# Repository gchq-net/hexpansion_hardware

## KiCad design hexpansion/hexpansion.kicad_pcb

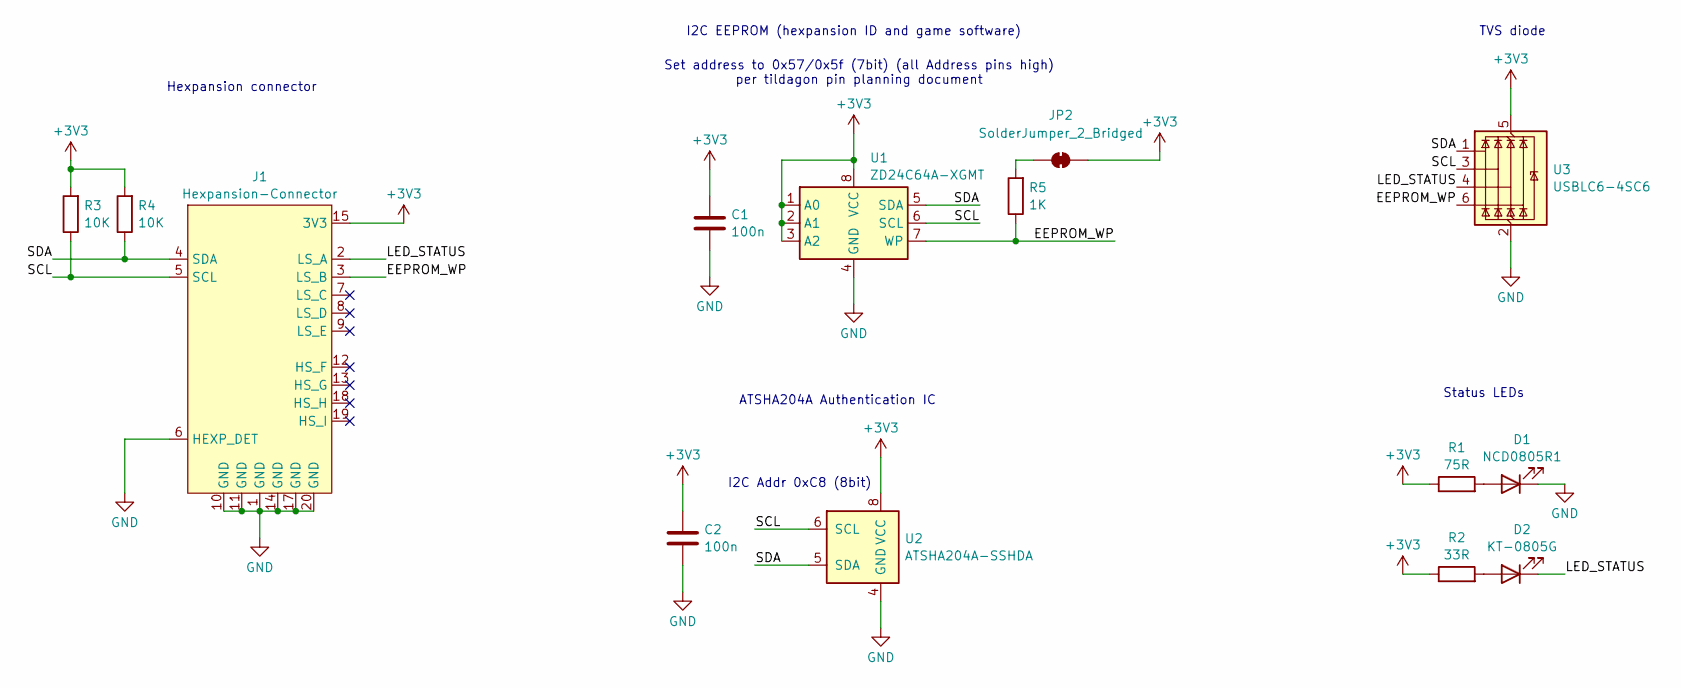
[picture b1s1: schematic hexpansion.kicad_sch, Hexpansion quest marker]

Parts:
C1, C2: 100n; C_0603_1608Metric
D1: NCD0805R1; LED_0805_2012Metric
D2: KT-0805G; LED_0805_2012Metric
J1: Hexpansion-Connector; hexpansion-edge-connector
JP2: SolderJumper_2_Bridged; SolderJumper-2_P1.3mm_Bridged_RoundedPad1.0x1.5mm
R1: 75R; R_0603_1608Metric
R2: 33R; R_0603_1608Metric
R3, R4: 10K; R_0603_1608Metric
R5: 1K; R_0603_1608Metric
U1: ZD24C64A-XGMT; TSSOP-8_4.4x3mm_P0.65mm
U2: ATSHA204A-SSHDA; SOIC-8_3.9x4.9mm_P1.27mm
U3: USBLC6-4SC6; SOT-23-6

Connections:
+3V3: C1.1, C2.1, J1.15 (3V3), J1.16 (3V3), JP2.2 (B), R1.1, R2.1, R3.2, R4.2, U1.1 (A0), U1.2 (A1), U1.3 (A2), U1.8 (VCC), U2.8 (VCC), U3.5 (VBUS)
/EEPROM_WP: J1.3 (LS_B), R5.1, U1.7 (WP), U3.6 (I/O4)
/LED_STATUS: D2.1 (K), J1.2 (LS_A), U3.4 (I/O3)
/SCL: J1.5 (SCL), R3.1, U1.6 (SCL), U2.6 (SCL), U3.3 (I/O2)
/SDA: J1.4 (SDA), R4.1, U1.5 (SDA), U2.5 (SDA), U3.1 (I/O1)
GND: C1.2, C2.2, D1.1 (K), J1.1 (GND), J1.6 (HEXP_DET), J1.10 (GND), J1.11 (GND), J1.14 (GND), J1.17 (GND), J1.20 (GND), U1.4 (GND), U2.4 (GND), U3.2 (GND)
unnamed: D1.2 (A), R1.2
unnamed: D2.2 (A), R2.2
unnamed: JP2.1 (A), R5.2

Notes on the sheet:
ATSHA204A Authentication IC
Set address to 0x57/0x5f (7bit) (all Address pins high) per tildagon pin planning document
I2C Addr 0xC8 (8bit)
Status LEDs
Hexpansion connector
I2C EEPROM (hexpansion ID and game software)
TVS diode

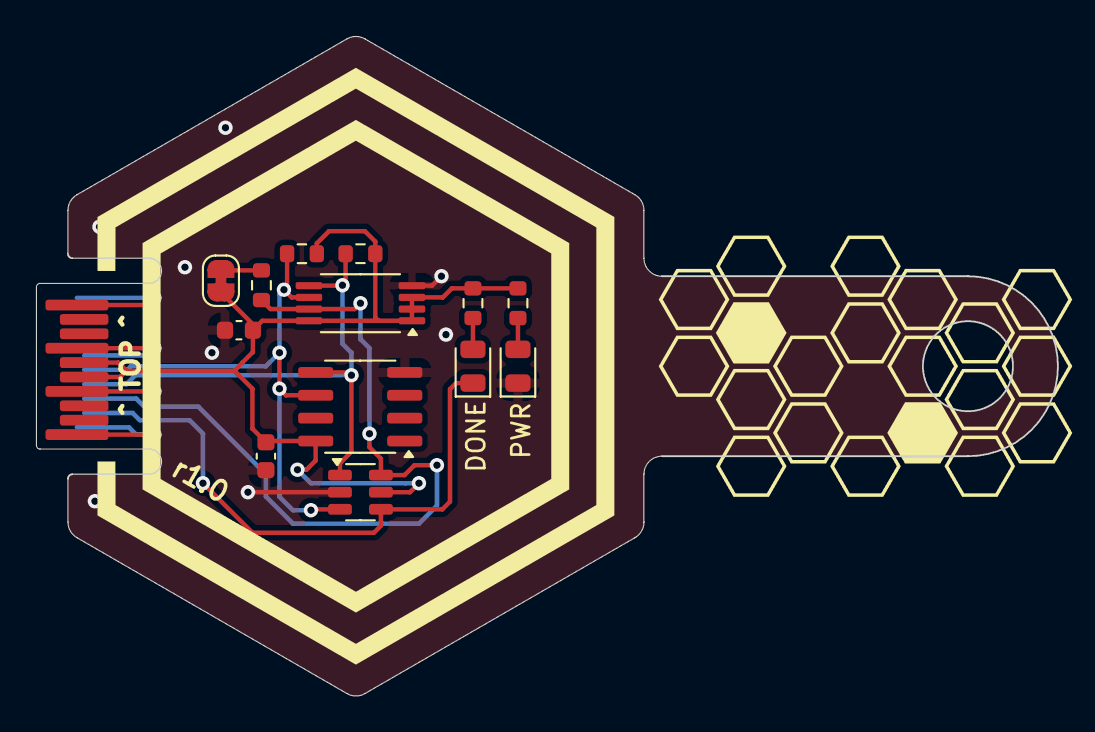
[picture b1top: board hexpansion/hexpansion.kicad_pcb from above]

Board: 2 copper layers, 56.7 x 36.6 mm, 14 parts (0 on the bottom side), 9 nets.

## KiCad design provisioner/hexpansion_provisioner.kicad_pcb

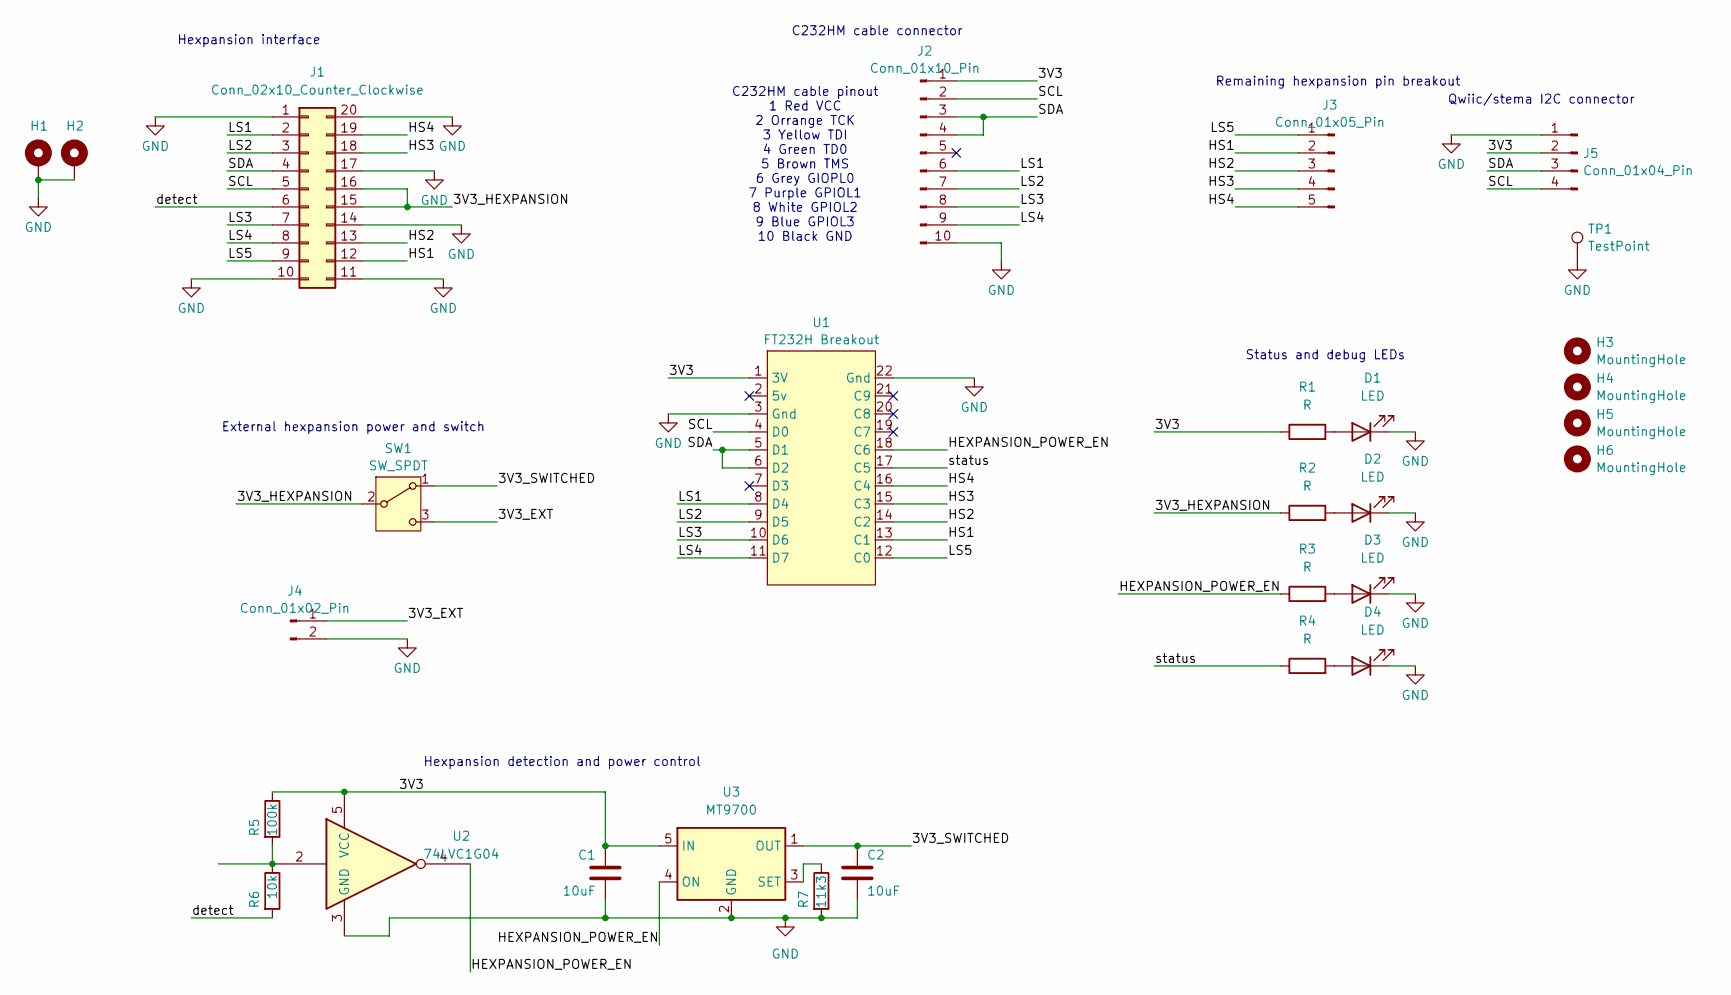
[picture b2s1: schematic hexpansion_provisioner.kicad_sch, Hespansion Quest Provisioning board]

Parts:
C1, C2: 10uF; C_1206_3216Metric
D1, D2, D3, D4: LED; LED_0805_2012Metric
H1, H2: MountingHole_Pad; SMTSO2030CTJ
H3, H4, H5, H6: MountingHole; MountingHole_2.7mm_M2.5
J1: Conn_02x10_Counter_Clockwise; SFP
J2: Conn_01x10_Pin; PinHeader_1x10_P2.54mm_Vertical
J3: Conn_01x05_Pin; PinHeader_1x05_P2.54mm_Vertical
J4: Conn_01x02_Pin; PinHeader_1x02_P2.54mm_Vertical
J5: Conn_01x04_Pin; JST_SH_SM04B-SRSS-TB_1x04-1MP_P1.00mm_Horizontal
R1, R2, R3, R4: R; R_0603_1608Metric
R5: 100k; R_0402_1005Metric
R6: 10k; R_0402_1005Metric
R7: 11k3; R_0603_1608Metric
SW1: SW_SPDT; SW_SPDT_PCM12
TP1: TestPoint; TestPoint_Bridge_Pitch5.08mm_Drill0.7mm
U1: FT232H Breakout; Adafruit_2264_v2
U2: 74LVC1G04; SOT-23-5
U3: MT9700; SOT-23-5

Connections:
/3V3: C1.1, J2.1, J5.2, R1.1, R5.1, U1.1 (3V), U2.5 (VCC), U3.5 (IN)
/3V3_EXT: J4.1, SW1.3 (C)
/3V3_HEXPANSION: J1.15, J1.16, R2.1, SW1.2 (B)
/3V3_SWITCHED: C2.1, SW1.1 (A), U3.1 (OUT)
/HEXPANSION_POWER_EN: R3.1, U1.18 (C6), U2.4, U3.4 (ON)
/HS1: J1.12, J3.2, U1.13 (C1)
/HS2: J1.13, J3.3, U1.14 (C2)
/HS3: J1.18, J3.4, U1.15 (C3)
/HS4: J1.19, J3.5, U1.16 (C4)
/LS1: J1.2, J2.6, U1.8 (D4)
/LS2: J1.3, J2.7, U1.9 (D5)
/LS3: J1.7, J2.8, U1.10 (D6)
/LS4: J1.8, J2.9, U1.11 (D7)
/LS5: J1.9, J3.1, U1.12 (C0)
/SCL: J1.5, J2.2, J5.4, U1.4 (D0)
/SDA: J1.4, J2.3, J2.4, J5.3, U1.5 (D1), U1.6 (D2)
/detect: J1.6, R6.2
/status: R4.1, U1.17 (C5)
GND: C1.2, C2.2, D1.1 (K), D2.1 (K), D3.1 (K), D4.1 (K), H1.1, H2.1, J1.1, J1.10, J1.11, J1.14, J1.17, J1.20, J2.10, J4.2, J5.1, R7.2, TP1.1, U1.3 (Gnd), U1.22 (Gnd), U2.3 (GND), U3.2 (GND)
unnamed: D1.2 (A), R1.2
unnamed: D2.2 (A), R2.2
unnamed: D3.2 (A), R3.2
unnamed: D4.2 (A), R4.2
unnamed: R5.2, R6.1, U2.2
unnamed: R7.1, U3.3 (SET)

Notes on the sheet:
C232HM cable connector
External hexpansion power and switch
Hexpansion detection and power control
Qwiic/stema I2C connector
C232HM cable pinout 1 Red VCC 2 Orrange TCK 3 Yellow TDI 4 Green TD0 5 Brown TMS 6 Grey GIOPL0 7 Purple GPIOL1 8 White GPIOL2 9 Blue GPIOL3 10 Black GND
Hexpansion interface
Status and debug LEDs
Remaining hexpansion pin breakout

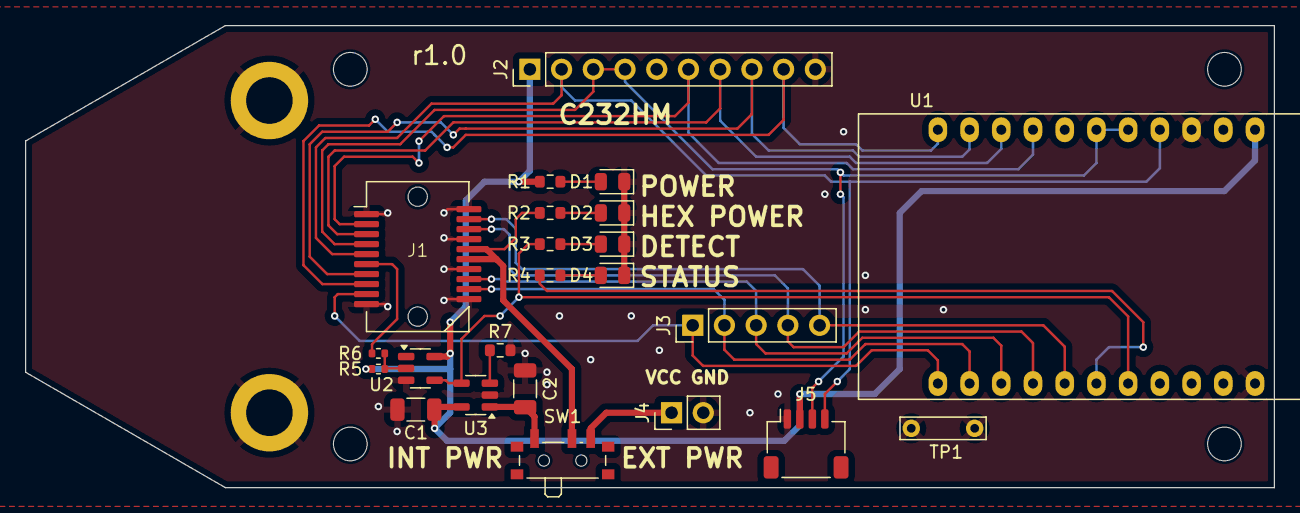
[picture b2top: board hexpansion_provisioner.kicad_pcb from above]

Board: 2 copper layers, 100.0 x 37.0 mm, 29 parts (0 on the bottom side), 25 nets.

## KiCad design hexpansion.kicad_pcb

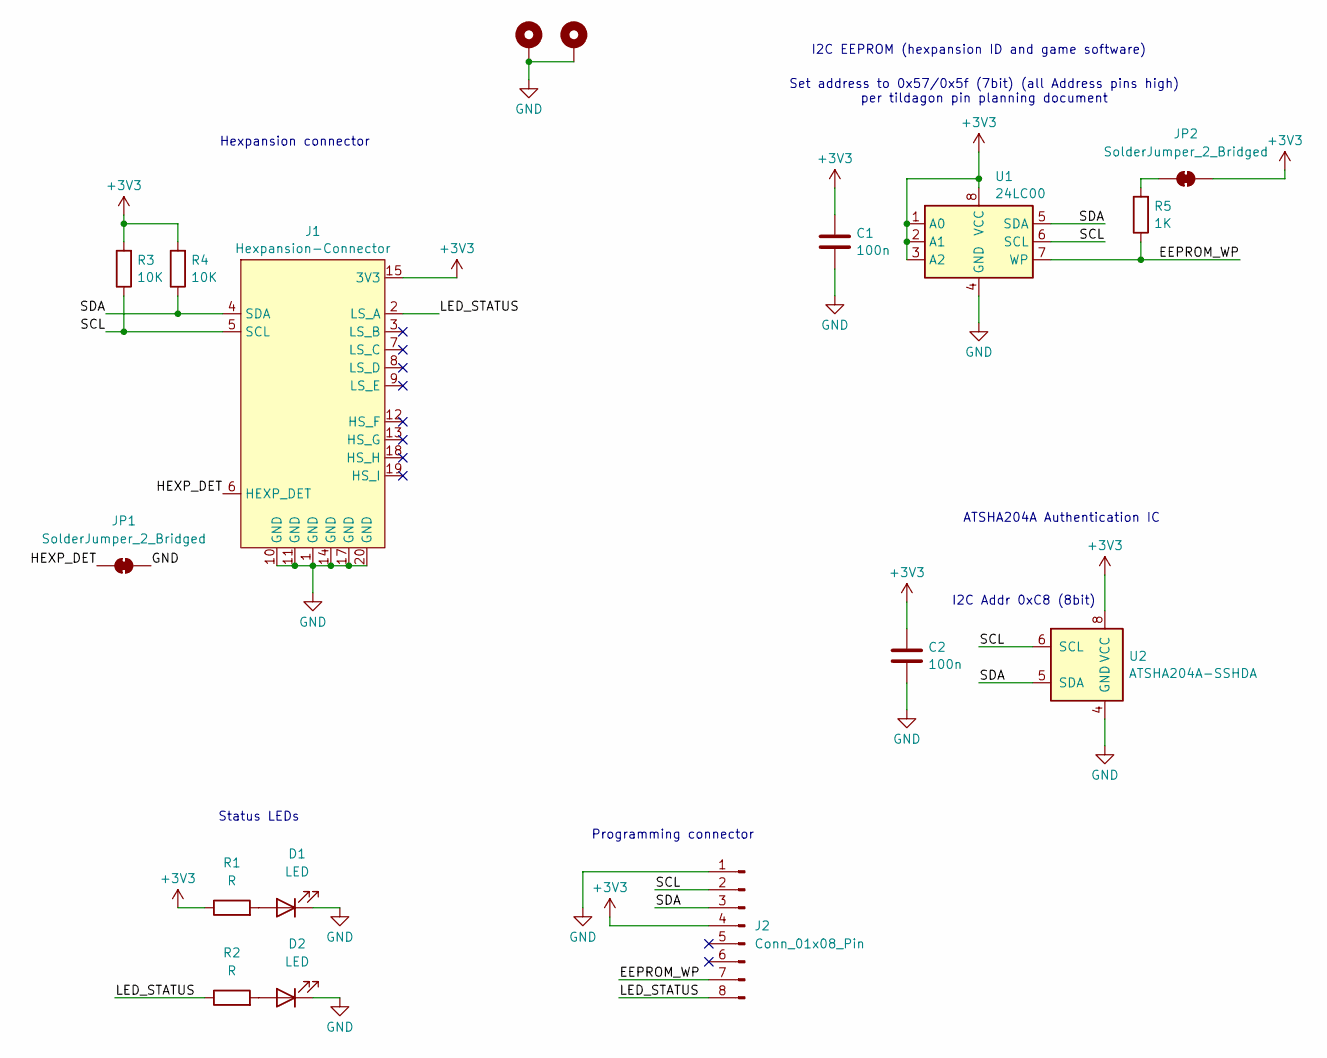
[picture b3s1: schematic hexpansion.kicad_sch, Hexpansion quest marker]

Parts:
C1, C2: 100n; C_0603_1608Metric
D1, D2: LED; LED_0805_2012Metric
H1, H2: MountingHole_Pad; MountingHole_2.2mm_M2_Pad_Via
J1: Hexpansion-Connector; hexpansion-edge-connector
J2: Conn_01x08_Pin; SOIC_clipProgSmall
JP1, JP2: SolderJumper_2_Bridged; SolderJumper-2_P1.3mm_Bridged_RoundedPad1.0x1.5mm
R1, R2: R; R_0603_1608Metric
R3, R4: 10K; R_0603_1608Metric
R5: 1K; R_0603_1608Metric
U1: 24LC00; TSSOP-8_4.4x3mm_P0.65mm
U2: ATSHA204A-SSHDA; SOIC-8_3.9x4.9mm_P1.27mm

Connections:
+3V3: C1.1, C2.1, J1.15 (3V3), J1.16 (3V3), J2.4, JP2.2 (B), R1.1, R3.2, R4.2, U1.1 (A0), U1.2 (A1), U1.3 (A2), U1.8 (VCC), U2.8 (VCC)
/EEPROM_WP: J2.7, R5.1, U1.7 (WP)
/HEXP_DET: J1.6 (HEXP_DET), JP1.1 (A)
/LED_STATUS: J1.2 (LS_A), J2.8, R2.1
/SCL: J1.5 (SCL), J2.2, R3.1, U1.6 (SCL), U2.6 (SCL)
/SDA: J1.4 (SDA), J2.3, R4.1, U1.5 (SDA), U2.5 (SDA)
GND: C1.2, C2.2, D1.1 (K), D2.1 (K), H1.1, H2.1, J1.1 (GND), J1.10 (GND), J1.11 (GND), J1.14 (GND), J1.17 (GND), J1.20 (GND), J2.1, JP1.2 (B), U1.4 (GND), U2.4 (GND)
unnamed: D1.2 (A), R1.2
unnamed: D2.2 (A), R2.2
unnamed: JP2.1 (A), R5.2

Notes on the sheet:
ATSHA204A Authentication IC
Set address to 0x57/0x5f (7bit) (all Address pins high) per tildagon pin planning document
Programming connector
I2C Addr 0xC8 (8bit)
Status LEDs
Hexpansion connector
I2C EEPROM (hexpansion ID and game software)

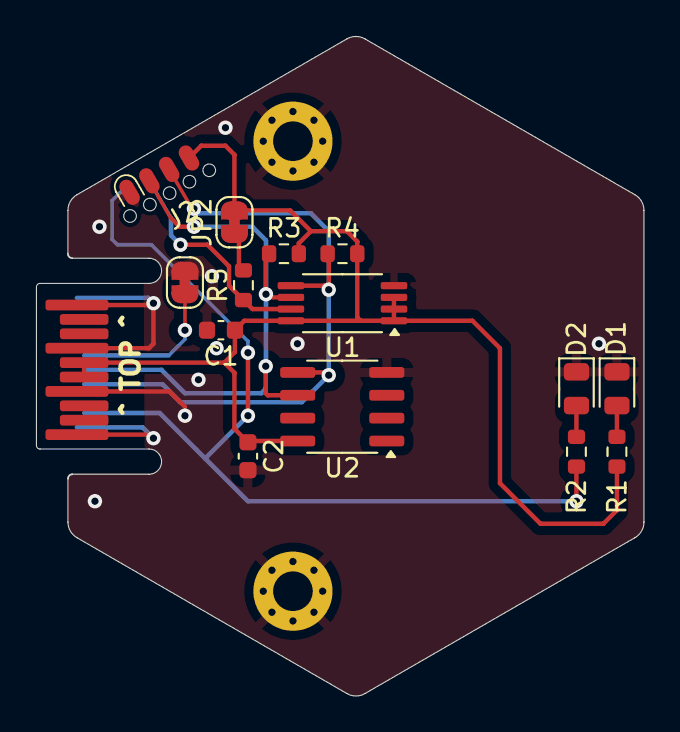
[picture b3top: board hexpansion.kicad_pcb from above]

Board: 2 copper layers, 33.7 x 36.6 mm, 17 parts (0 on the bottom side), 10 nets.

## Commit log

2024-04-13 Added initial schematic and layout
2024-04-24 Move hexpansion files into subfolder
2024-04-24 Add PCB design for provisioner board
2024-04-24 Add adafruit breakout symbol
2024-04-24 Update hexpansion design
    Adds TVS diode
    Removes seperate programming connector
    tidy up PCB layout
2024-04-27 Add pcb arwork and prep for manufacture.
